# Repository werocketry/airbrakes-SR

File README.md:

# airbrakes-SR

This is the repository for the Western Engineering Rocketry Team's design of an airbrakes system.

## Sister Projects

- [werocketry/RocketFlightSim](https://github.com/werocketry/RocketFlightSim)
- [werocketry/HPR-Rocket-Flight-Computer](https://github.com/werocketry/HPR-Rocket-Flight-Computer)

## Acronyms of the Trade
| Acronym | Full Name                                 | Description                                                                          |
|---------|-------------------------------------------|--------------------------------------------------------------------------------------|
| AGL     | Above Ground Level                        |                                                                                      |
| COTS    | Commercial off-the-shelf                  |                                                                                      |
| CP      | Center of pressure                        |                                                                                      |
| ESRA    | Experimental Sounding Rocket Association  |                                                                                      |
| FOS     | Factor of Safety                          |                                                                                      |
| FS      | Factor of Safety                          |                                                                                      |
| IREC    | Intercollegiate Rocket Engineering Competition | Basically SAC. It used to happen somewhere else                                       |
| NM      | New Mexico                                |                                                                                      |
| NMSU    | New Mexico State University               | The university on whose grounds some parts of SAC are held                           |
| OR      | OpenRocket                                |                                                                                      |
| .ork    | OpenRocket filetype                       |                                                                                      |
| RSO     | Range Safety Officer                      | The person that gives you permission to launch                                       |
| SA      | Spaceport America                         | The launch site where SAC is hosted                                                  |
| SAC     | Spaceport America Cup                     |                                                                                      |
| SRAD    | Student researched and designed           |                                                                                      |
| VLA     | Vertical Launch Area                      |                                                                                      |
| WERT    | Western Engineering Rocketry Team         | Also called WE Rocketry                                                              |

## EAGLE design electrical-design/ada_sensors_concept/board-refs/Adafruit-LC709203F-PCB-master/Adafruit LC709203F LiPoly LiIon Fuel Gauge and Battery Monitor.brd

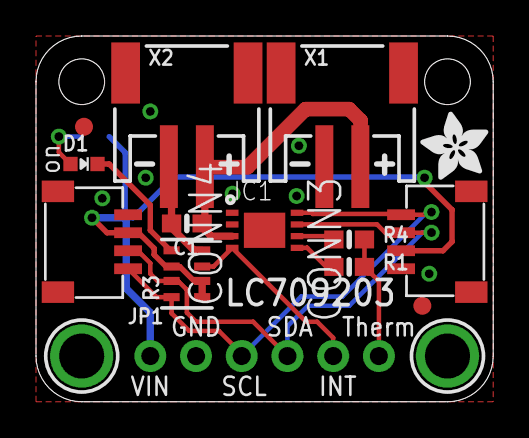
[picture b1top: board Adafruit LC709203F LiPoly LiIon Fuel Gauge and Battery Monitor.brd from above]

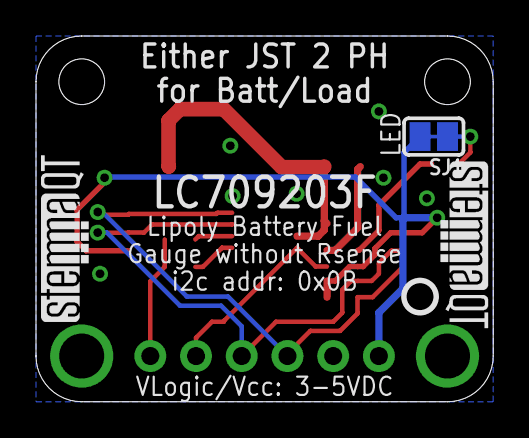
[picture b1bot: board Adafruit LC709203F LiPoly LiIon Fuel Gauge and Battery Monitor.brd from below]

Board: 2 copper layers, 25.4 x 20.3 mm, 20 parts (4 on the bottom side), 11 nets.

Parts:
C1: 1uF; 0603-NO
CONN3, CONN4: STEMMA_I2C_QT; JST_SH4
D1: GREEN; CHIPLED_0603_NOOUTLINE
FID3, FID4: FIDUCIAL_1MM
IC1: LC709203F; WDFN8_3X4_0.65
JP1: 1X06_ROUND_70
R1: 10K; 0603-NO
R3: 10K; RESPACK_4X0603
R4: 100; 0603-NO
SJ1: SOLDERJUMPER_CLOSEDWIRE
U$19, U$21: MOUNTINGHOLE2.5; MOUNTINGHOLE_2.5_PLATED
U$22: ADAFRUIT_3.5MM
U$25: PCBFEAT-REV-040
U$30, U$31: STEMMAQT
X1, X2: JST 2 PH; JSTPH2_BATT

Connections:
GND: C1.2, CONN3.1, CONN4.1, IC1.1, IC1.2, JP1.2, R3.4, X1.1, X2.1
INT: IC1.4, JP1.5, R3.3
unnamed: D1.C, R3.5
unnamed: D1.A, SJ1.1
SCL: CONN3.4, CONN4.4, IC1.8, JP1.3, R3.8
SDA: CONN3.3, CONN4.3, IC1.7, JP1.4, R3.7
THERM: JP1.6, R1.2, R4.2
TSENSE: IC1.6, R4.1
TSW: IC1.5, R1.1
VBAT: C1.1, IC1.3, X1.2, X2.2
VCC: CONN3.2, CONN4.2, JP1.1, R3.1, R3.2, R3.6, SJ1.2

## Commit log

2023-10-13 modified: README.md
2023-10-13 modified: data_manip.ipynb
2023-10-16 Added flaps taking time to deploy to PID simulation
2023-10-16 Minor parameter adjustments
2023-10-16 Added drag to custom flight profile during ascent
2023-10-16 Controller now outputs max deployment angle after target apogee
2023-10-17 optimizations, minor enhancements
2023-10-17 New folder for prelim flight analysis
2023-10-17 Rename data_manip.ipynb to preliminary_flight_analysis/data_manip.ipynb
2023-10-17 Rename README.md to preliminary_flight_analysis/README.md
2023-10-18 added sensor / board documentation & design files
2023-10-20 changed airbrake parameters
2023-10-20 minor changes
2023-10-20 rearrange
2023-10-21 save time
2023-11-05 parameter updates, notebook shows more data
2023-11-10 Provide more information, update parameters, make better use of telemega and telemetrum datasets
2023-11-10 cleaned up, easier to set up custom sims
2023-11-10 misc updates
2023-11-11 Towards a dynamic Cd_rocket
2023-11-12 Improved simulation, more detailed analysis
2023-11-13 minor
2023-11-13 q in final graphs instead of speed
2023-11-14 improved flight simulation
2023-11-14 more accurate sim
2023-11-15 added tutorial to get started on windows
2023-11-20 minor update
2023-11-20 add Prometheus ORK file
2023-11-21 checkpoint save
2023-11-22 refactored simulation into seperate file added consideration for launch angle off the vertical in sim various minor updates
2023-11-23 minor cleanup
2023-11-27 moved running ideas list into repo
2023-12-02 first sim of Hyperion
2023-12-05 added electrical schematic start and resources
2023-12-06 rename data_manip
2024-01-03 fixed visualizations calling of ascent simulation with airbrakes to use the proper rocket parameters (not always Prometheus')
2024-01-03 down to 3 flaps
2024-01-10 Cleanup
2024-01-11 Cross-sectional area now includes fins
2024-01-11 rename sim folder
2024-01-12 Misc improvements, cleanup
2024-01-14 launch angle now 10 deg off vertical updated airbrakes flap size
2024-01-15 launch rail length now accounts for added DOFs when only one launch lug left on rail (almost negligeable change ~10ft)
2024-01-15 created separate configs.py file to hold sets of parameters used to make instances of the custom classes
2024-01-16 added electrical sketch for controls
2024-01-18 did some refactoring of sims and repo structure
2024-01-18 refactored the flight sim file strcuture, added load analysis template
2024-01-18 minor formatting
2024-01-18 minor performance improvement
2024-01-18 Added STEP Files
2024-01-19 organized rest of functions including visualization
2024-01-19 Added Assemblies at different Angles
2024-01-19 minor wording changes
2024-01-19 load analysis outline complete - statics needs review
2024-01-19 added images and sources to load analysis
2024-01-19 load analysis statics fix
2024-01-19 load analysis updated
2024-01-20 updated analyses, an attempt at trying out servo and updated sims
2024-01-20 updated analyses, an attempt at trying out stepper and updated sims
2024-01-23 - Initial sensitivity analysis - Updated Hyperion's length - Fixed improper calling of simulate_airbrakes_flight in visualizations notebook
2024-01-23 small analyses of sensitivity analysis
2024-01-24 Updated Hyperion dry mass
2024-01-26 renamed "launch lug" to "rail button" (because that's what they are)
2024-01-28 prep for updatable configs
2024-02-04 - updated Hyperion mass - updated sensitivity analysis
2024-02-09 updated pressures and temperatures used in sensitivity analysis
2024-02-10 added stopping power analysis
2024-02-11 added battery design work
2024-02-12 - option for variations in sensitivity analysis to be drawn from a gaussian instead of just a linspace - added wind correction (flat -300 ft) to stopping power sim
2024-02-13 began integration of aero simulations and load analysis
2024-02-16 optimizations to sim: - default timestep of simulation (with and without airbrakes) now 0.01 instead of 0.001 (they only differ by about 2m in apogee) - brought conversion to radians of parameters de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
2024-02-17 Small simulation efficieny improvement. Got rid of previous_height variable. Final loops now end at v_y <=0
2024-02-20 - cleaned up - fixed TeleMega data in visualizations_cleaned
2024-02-21 - added RocketPy sim - refactored classes, now have motor class
2024-02-21 - added Prometheus RocketPy sim - some organization
2024-02-22 added airbrakes to RocketPy sim
2024-02-27 added some more stuff for motor analysis
2024-03-05 added some parts for data collection
2024-03-05 start of sim that might be put on the controller
2024-03-06 updated rocket mass and engine dry mass
2024-03-06 ran rocketpy sim with new masses, updated notebook
2024-03-10 added electrical schematic
2024-03-11 - updated airbrake parameters - minor other changes
2024-03-12 updated onboard flight sim
2024-03-12 added software libs
2024-03-12 - fixed outdated static call of flap area in load analysis within flight-simulator directory - cleanup -added ideas, TODOs to track what still needs doing - various minor changes
2024-03-14 Added a more precise temperature lapse rate
2024-03-17 updates to ece
2024-03-18 motor servo software updates
2024-03-20 - updated rocket mass - added a little to controller flight simulator - minor edits
2024-03-20 added altitude estimator test
2024-03-20 ported std devs script and got 2/3 working
2024-03-21 - updated airbrakes flap area, rocket fin thickness, rocket mass - updates to RocketPy parameters
2024-03-22 software controls changes
2024-03-26 added some Cd curves from ork
2024-03-28 Fixed Cd from Re in RocketPy sim
2024-03-29 changed default sim timestep, other minor tweaks
2024-03-30 begin implementing lookup tables
2024-03-31 ability to determine deployment angles for lookup tables
2024-03-31 more granular and efficient generation of deployment angle lookups
2024-03-31 made first lookup table
2024-03-31 changed lookup table location
2024-03-31 changed lookup table directory to flight-simulator
2024-04-02 software tweaks and development of A4957 custom driver
2024-04-02 v2 of circuit for PCB
2024-04-02 removed old log file
2024-04-03 created all PCB footprints
2024-04-04 bulk of PCB design layout complete
2024-04-04 PCB work
2024-04-05 completed motor driver PCB
2024-04-06 software dir refactoring before flight computer merge
2024-04-08 rewrote sim, classes, and other scripts to take Cd as a function of Ma instead of Re
2024-04-09 sim updates for force analysis and visual clean up on elec drawings
2024-04-09 added max theoretical calcs for g-force and q, other minor changes
2024-04-09 Initial commit splitting capstone repo
2024-04-20 transfer and beef up of documentation
2024-04-20 Configure LFS to track SolidWorks, STEP, and STL files
2024-04-20 Update README.md with sister project links
2024-04-21 minor documentation updates
2024-04-22 moved controller flight simulator, this year's configs, and lookup table generator to airbrakes repo from flight sim repo
2024-04-23 added note about rocket characteristics to wind tunnel test plan
2024-04-24 changed some notes about future work in two files
2024-04-24 added a few things from Teams, minor fixes to docs
2024-05-08 updated launch conditions for RFS' new generalized local gravity and temp lapse rate
2024-05-09 updated Hyperion values
2024-05-11 specify launch conditions for sim
2024-05-13 rocketpy sims updates
2024-05-14 updated RocketPy sims
2024-05-15 Prometheus RocketPy fins adjusted
2024-05-16 fix for visualizing Prometheus flight data
2024-05-16 updated visualizations to new Hyperion parameters, fixed bug when plotting aerodynamics in metric
2024-05-22 updated to use rocketflightsim as a package
2024-05-23 Added minor note about possible future use of Prometheus data in airbrakes simulations
2024-05-26 updated sims with newest mass budget
2024-05-27 updated sims with newest mass budget, newest updates to RFS
2024-05-29 updated configs, simulations with newest mass updates
2024-05-31 update sims with newest version of RFS
2024-06-02 updated sims with new launch angle
2024-06-08 updates of configs with new masses, updates of sims, start of new advanced lookup table generation
2024-06-11 updated sims with new drag curve
2024-06-13 added minor note to self
2024-06-18 cleaned configs for comp
2024-06-18 Tuesday morning updates to configs, sensitivity analysis
2024-06-22 final updates from competition
2024-07-05 addition of Hyperion flight data

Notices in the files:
parts and their libraries:
microbuilder: This work is placed in the public domain, and may be freely used for commercial and non-commercial work with the following conditions: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
